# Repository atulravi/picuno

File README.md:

# PicUNO Series Of Boards By AtrivaTECH

AtrivaTECH Aims to bring the latest and greatest processors, chipsets and microcontrollers in the Custom PicUNO form factor derived from the Arduino UNO Form Factor. 

The PicUNO Line-Up of Open Source boards is as follows:
## Boards
1) RP2040 - https://github.com/atulravi/picuno/tree/main/RP2040
## Shields 
1) Lattice ICE50UP5K FPGA Shield - https://github.com/atulravi/picuno-ice
<br>
Current Version Under Test: V3.0.0 (RP2040)

## Information:

As development is consistent, documenting it, is not. To combat the same, various repositories and their purposes are given below. You may Follow the ones of choice to be notified when latest versions/updates are pushed.
1) Circuit Python port: https://github.com/atulravi/circuitpython
2) MicroPython Port: https://github.com/AtrivaTECH/micropython/tree/master
3) Arduino IDE Library: https://github.com/AtrivaTECH/AtrivaTECH_PicUNO
4) Documentation: https://github.com/AtrivaTECH/picuno-documentation
5) Project Repository: https://github.com/AtrivaTECH/picuno-projects
6) FPGA Shield: https://github.com/AtrivaTECH/picuno-ice

## Honorable Certifications:

## In The Press

Hackster.io- "Atul Ravi's PicUNO is a Pico-style RP2040 board in the popular Arduino form factor with extra features."

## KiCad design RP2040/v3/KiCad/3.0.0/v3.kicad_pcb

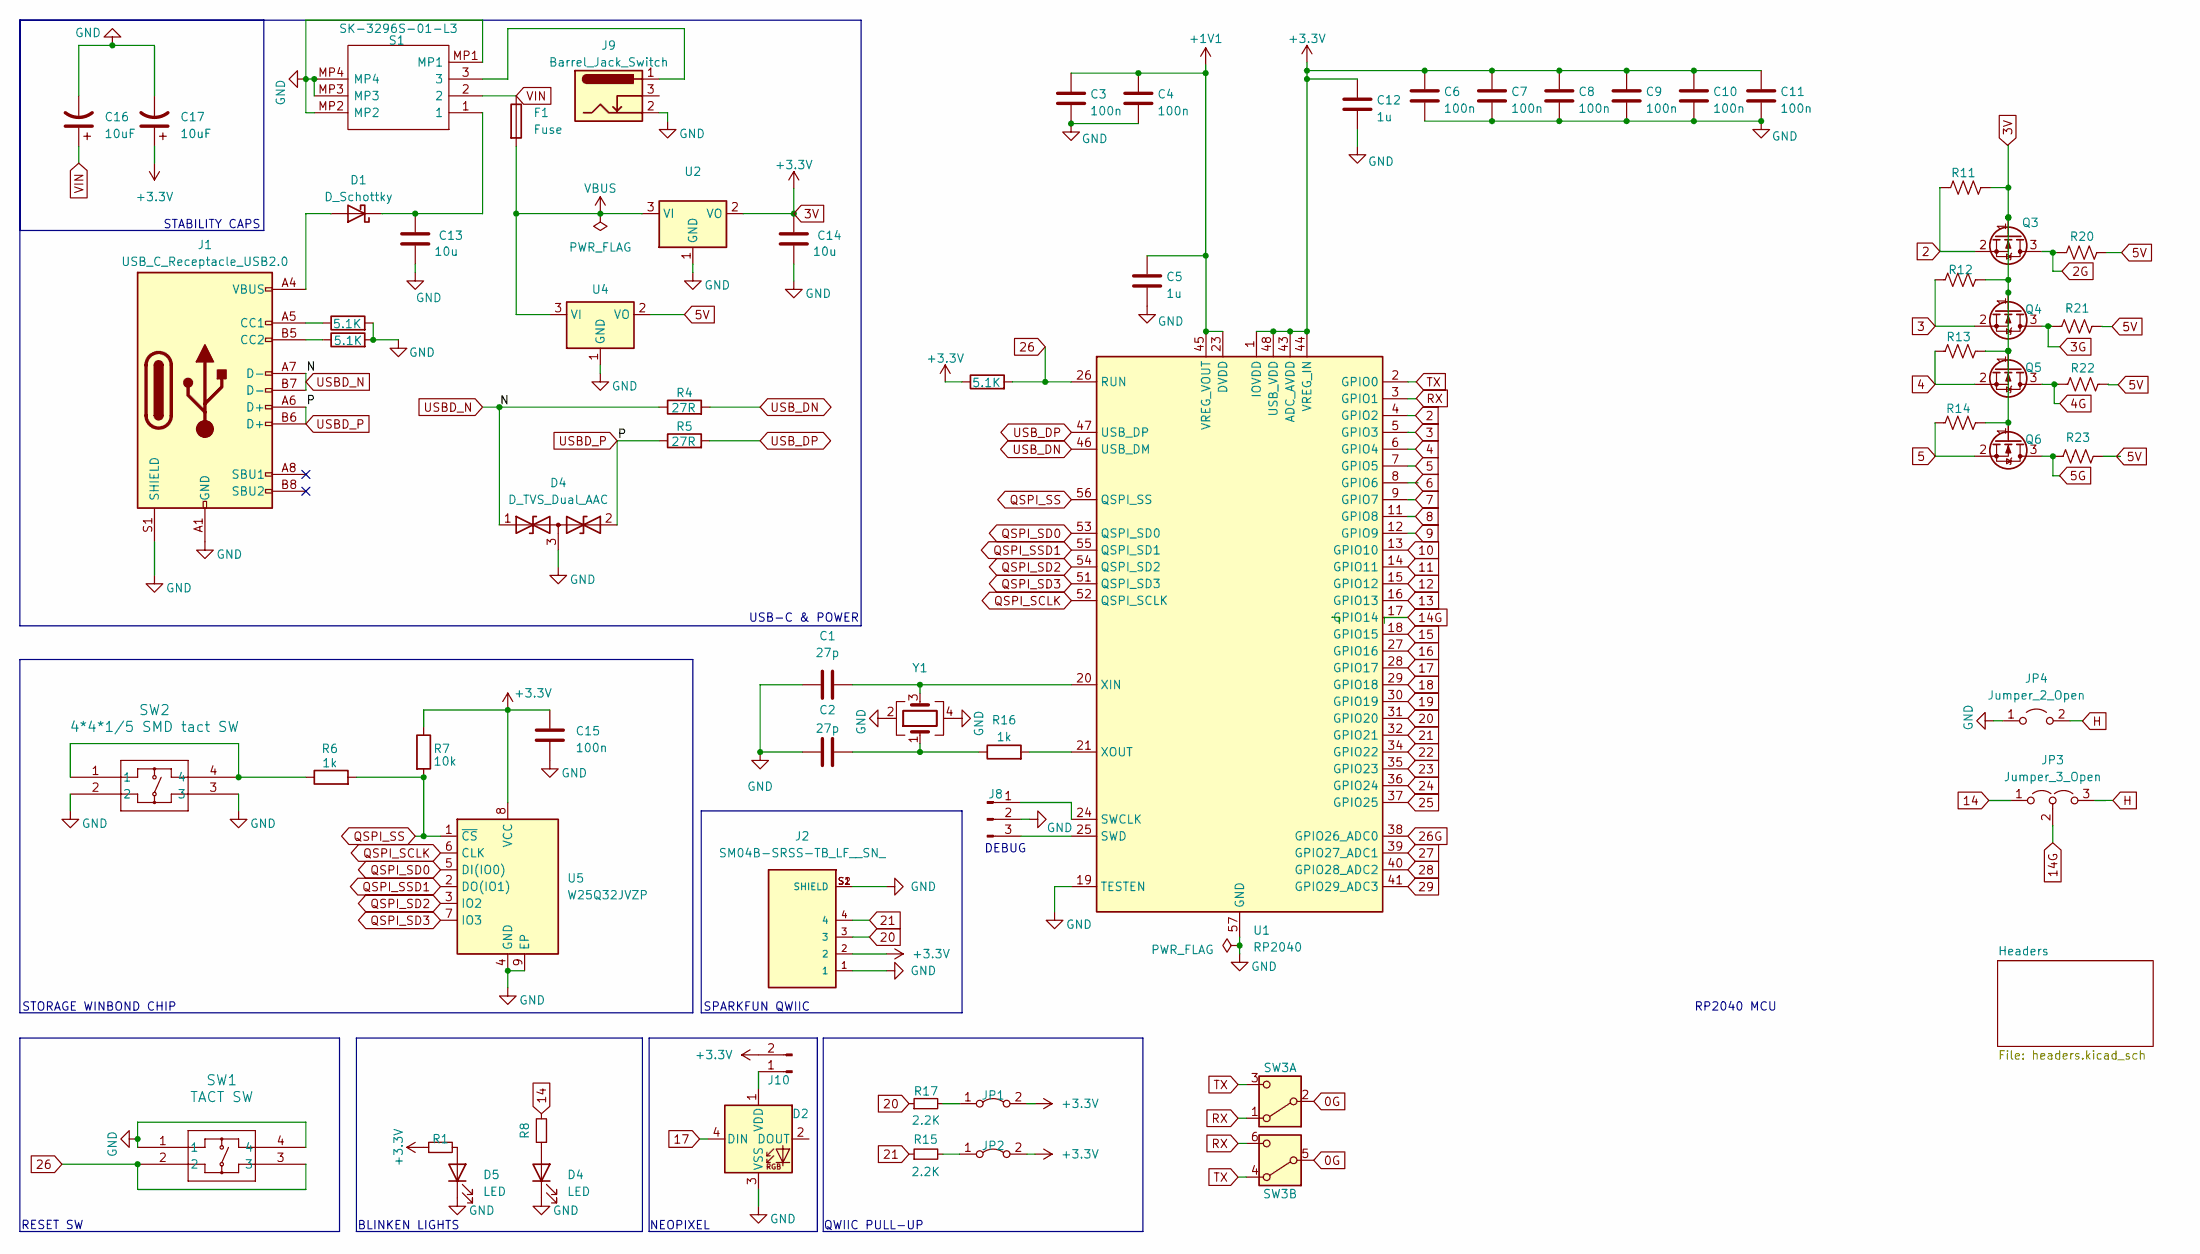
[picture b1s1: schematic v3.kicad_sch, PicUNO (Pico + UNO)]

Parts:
C1, C2: 27p; C_0402_1005Metric_Pad0.74x0.62mm_HandSolder
C3, C4, C6, C7, C8, C9, C10, C11, C15: 100n; C_0402_1005Metric_Pad0.74x0.62mm_HandSolder
C5, C12: 1u; C_0402_1005Metric_Pad0.74x0.62mm_HandSolder
C13, C14: 10u; C_0402_1005Metric_Pad0.74x0.62mm_HandSolder
C16, C17: 10uF; CP_Elec_4x5.4; LCSC C4747971
D1: D_Schottky; D_SOD-128
D2: WS2812B; LED_WS2812B_PLCC4_5.0x5.0mm_P3.2mm
D4: D_TVS_Dual_AAC; SOT-23
D5: LED; LED_0805_2012Metric_Pad1.15x1.40mm_HandSolder
F1: Fuse; Fuse_1206_3216Metric_Pad1.42x1.75mm_HandSolder
J1: USB_C_Receptacle_USB2.0; USB_C_Receptacle_G-Switch_GT-USB-7010ASV
J2: SM04B-SRSS-TB_LF__SN_; JST_SM04B-SRSS-TB_LF__SN_
J8: Conn_01x03_Pin; PinSocket_1x03_P2.54mm_Vertical
J9: Barrel_Jack_Switch; BarrelJack_Horizontal
J10: Conn_01x02_Pin; PinHeader_1x02_P2.54mm_Vertical
JP1, JP2: Jumper_2_Bridged; SolderJumper-2_P1.3mm_Open_RoundedPad1.0x1.5mm
JP3: Jumper_3_Open; SolderJumper-3_P1.3mm_Open_Pad1.0x1.5mm
JP4: Jumper_2_Open; SolderJumper-2_P1.3mm_Open_RoundedPad1.0x1.5mm
Q3, Q4, Q5, Q6: BSS138; SOT-23
R1, R8: 220; R_0402_1005Metric_Pad0.72x0.64mm_HandSolder
R2, R3, R33: 5.1K; R_0402_1005Metric_Pad0.72x0.64mm_HandSolder
R4, R5: 27R; R_0402_1005Metric_Pad0.72x0.64mm_HandSolder
R6, R16: 1k; R_0402_1005Metric_Pad0.72x0.64mm_HandSolder
R7: 10k; R_0402_1005Metric_Pad0.72x0.64mm_HandSolder
R11, R12, R13, R14, R20, R21, R22, R23: 10K; R_0402_1005Metric_Pad0.72x0.64mm_HandSolder
R15, R17: 2.2K; R_0402_1005Metric_Pad0.72x0.64mm_HandSolder
S1: SK-3296S-01-L3; SK3296S01L3; Manufacturer_Part_Number SK-3296S-01-L3
SW1: TACT SW; SW_SPST_TL3342
SW2: 4*4*1/5 SMD tact SW; SW_SPST_TL3342
SW3: SW_DPDT_x2; SW_CL-SB-22A-02T; MFG Part No C2904912
U1: RP2040; QFN-56-1EP_7x7mm_P0.4mm_EP3.2x3.2mm
U2: AZ1117CH-3.3TRG1 SOT223-3; SOT-223-3_TabPin2
U4: AMS1117-5.0; SOT-223-3_TabPin2
U5: W25Q32JVZP; WSON-8-1EP_6x5mm_P1.27mm_EP3.4x4.3mm
Y1: \YSX321SL 12 Mhz; Crystal_SMD_3225-4Pin_3.2x2.5mm

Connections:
0G: SW3.2 (B), SW3.5 (B)
2: Q3.2 (S), R11.1, U1.4 (GPIO2)
2G: Q3.3 (D), R20.1
3: Q4.2 (S), R12.1, U1.5 (GPIO3)
3G: Q4.3 (D), R21.1
3V: C6.1, C7.1, C8.1, C9.1, C10.1, C11.1, C12.1, C14.1, C15.1, C17.1, J2.2, J10.2, JP1.2 (B), JP2.2 (B), Q3.1 (G), Q4.1 (G), Q5.1 (G), Q6.1 (G), R1.1, R7.1, R11.2, R12.2, R13.2, R14.2, R33.1, U1.1 (IOVDD), U1.10 (IOVDD), U1.22 (IOVDD), U1.33 (IOVDD), U1.42 (IOVDD), U1.43 (ADC_AVDD), U1.44 (VREG_IN), U1.48 (USB_VDD), U1.49 (IOVDD), U2.2 (VO), U5.8 (VCC); also elsewhere on the board
4: Q5.2 (S), R13.1, U1.6 (GPIO4)
4G: Q5.3 (D), R22.1
5: Q6.2 (S), R14.1, U1.7 (GPIO5)
5G: Q6.3 (D), R23.1
5V: R20.2, R21.2, R22.2, R23.2, U4.2 (VO); also elsewhere on the board
6: U1.8 (GPIO6)
7: U1.9 (GPIO7)
8: U1.11 (GPIO8)
9: U1.12 (GPIO9)
10: U1.13 (GPIO10)
11: U1.14 (GPIO11)
12: U1.15 (GPIO12)
13: U1.16 (GPIO13)
14: JP3.1 (A), R8.2
14G: JP3.2 (C), U1.17 (GPIO14)
15: U1.18 (GPIO15)
16: U1.27 (GPIO16)
17: D2.4 (DIN), U1.28 (GPIO17); also elsewhere on the board
18: U1.29 (GPIO18)
19: U1.30 (GPIO19)
20: J2.3, R17.1, U1.31 (GPIO20); also elsewhere on the board
21: J2.4, R15.1, U1.32 (GPIO21); also elsewhere on the board
22: U1.34 (GPIO22)
23: U1.35 (GPIO23)
24: U1.36 (GPIO24); also elsewhere on the board
25: U1.37 (GPIO25); also elsewhere on the board
26: R33.2, SW1.2, SW1.3, U1.26 (RUN); also elsewhere on the board
26G: U1.38 (GPIO26_ADC0)
27: U1.39 (GPIO27_ADC1)
28: U1.40 (GPIO28_ADC2)
29: U1.41 (GPIO29_ADC3)
+1V1: C3.1, C4.1, C5.1, U1.23 (DVDD), U1.45 (VREG_VOUT), U1.50 (DVDD)
H: JP3.3 (B), JP4.2 (B)
unnamed: C2.2, R16.1, Y1.1
unnamed: D1.2 (A), J1.A4 (VBUS), J1.A9 (VBUS), J1.B4 (VBUS), J1.B9 (VBUS)
unnamed: C13.1, D1.1 (K), S1.1
unnamed: D2.1 (VDD), J10.1
unnamed: D5.2 (A), R1.2
unnamed: J1.A5 (CC1), R2.1
unnamed: J1.B5 (CC2), R3.1
unnamed: J8.1, U1.24 (SWCLK)
unnamed: J8.3, U1.25 (SWD)
unnamed: J9.1, S1.3
unnamed: JP1.1 (A), R17.2
unnamed: JP2.1 (A), R15.2
unnamed: R6.1, SW2.1, SW2.4
unnamed: C1.2, U1.20 (XIN), Y1.3
unnamed: R16.2, U1.21 (XOUT)
QSPI_SCLK: U1.52 (QSPI_SCLK), U5.6 (CLK)
QSPI_SD0: U1.53 (QSPI_SD0), U5.5 (DI(IO0))
QSPI_SD2: U1.54 (QSPI_SD2), U5.3 (IO2)
QSPI_SD3: U1.51 (QSPI_SD3), U5.7 (IO3)
QSPI_SS: R6.2, R7.2, U1.56 (QSPI_SS), U5.1 (~CS)
QSPI_SSD1: U1.55 (QSPI_SD1), U5.2 (DO(IO1))
RX: SW3.1 (A), SW3.6 (C), U1.3 (GPIO1)
TX: SW3.3 (C), SW3.4 (A), U1.2 (GPIO0)
USB_DN: R4.2, U1.46 (USB_DM)
USB_DP: R5.2, U1.47 (USB_DP)
VBUS: F1.2, U2.3 (VI), U4.3 (VI)
VIN: C16.1, F1.1, S1.2; also elsewhere on the board

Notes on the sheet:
NEOPIXEL
RP2040 MCU
SPARKFUN QWIIC
STABILITY CAPS
RESET SW
DEBUG
STORAGE WINBOND CHIP
QWIIC PULL-UP
BLINKEN LIGHTS
USB-C & POWER

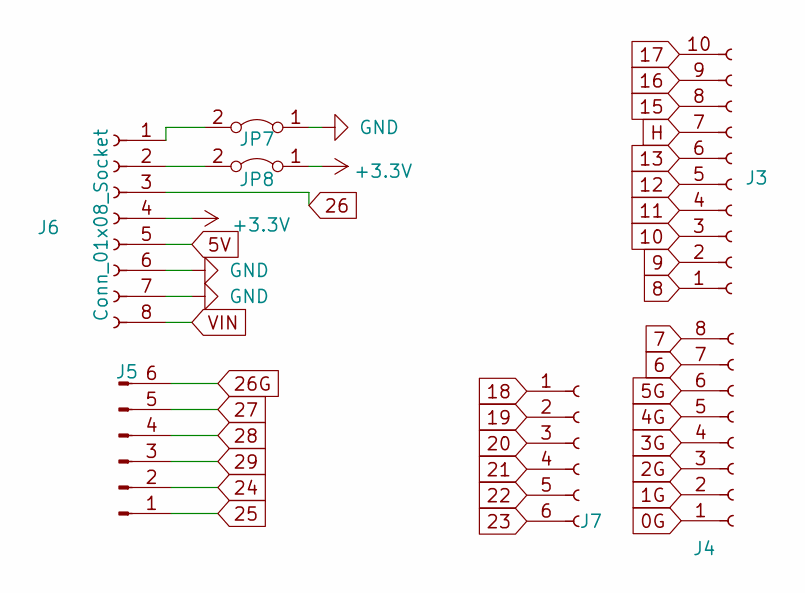
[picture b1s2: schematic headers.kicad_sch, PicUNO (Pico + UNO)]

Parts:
J3: Conn_01x10_Socket; PinSocket_1x10_P2.54mm_Vertical
J4, J6: Conn_01x08_Socket; PinSocket_1x08_P2.54mm_Vertical
J5: Conn_01x06_Pin; PinSocket_1x06_P2.54mm_Vertical
J7: Conn_01x06_Socket; PinSocket_1x06_P2.54mm_Vertical
JP7, JP8: Jumper_2_Bridged; SolderJumper-2_P1.3mm_Open_RoundedPad1.0x1.5mm

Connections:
3V: J6.4, JP8.1 (A); also elsewhere on the board
5V: J6.5; also elsewhere on the board
17: J3.10; also elsewhere on the board
20: J7.3; also elsewhere on the board
21: J7.4; also elsewhere on the board
24: J5.2; also elsewhere on the board
25: J5.1; also elsewhere on the board
26: J6.3; also elsewhere on the board
unnamed 67: J6.1, JP7.2 (B); also elsewhere on the board
unnamed 68: J6.2, JP8.2 (B); also elsewhere on the board
VIN: J6.8; also elsewhere on the board

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
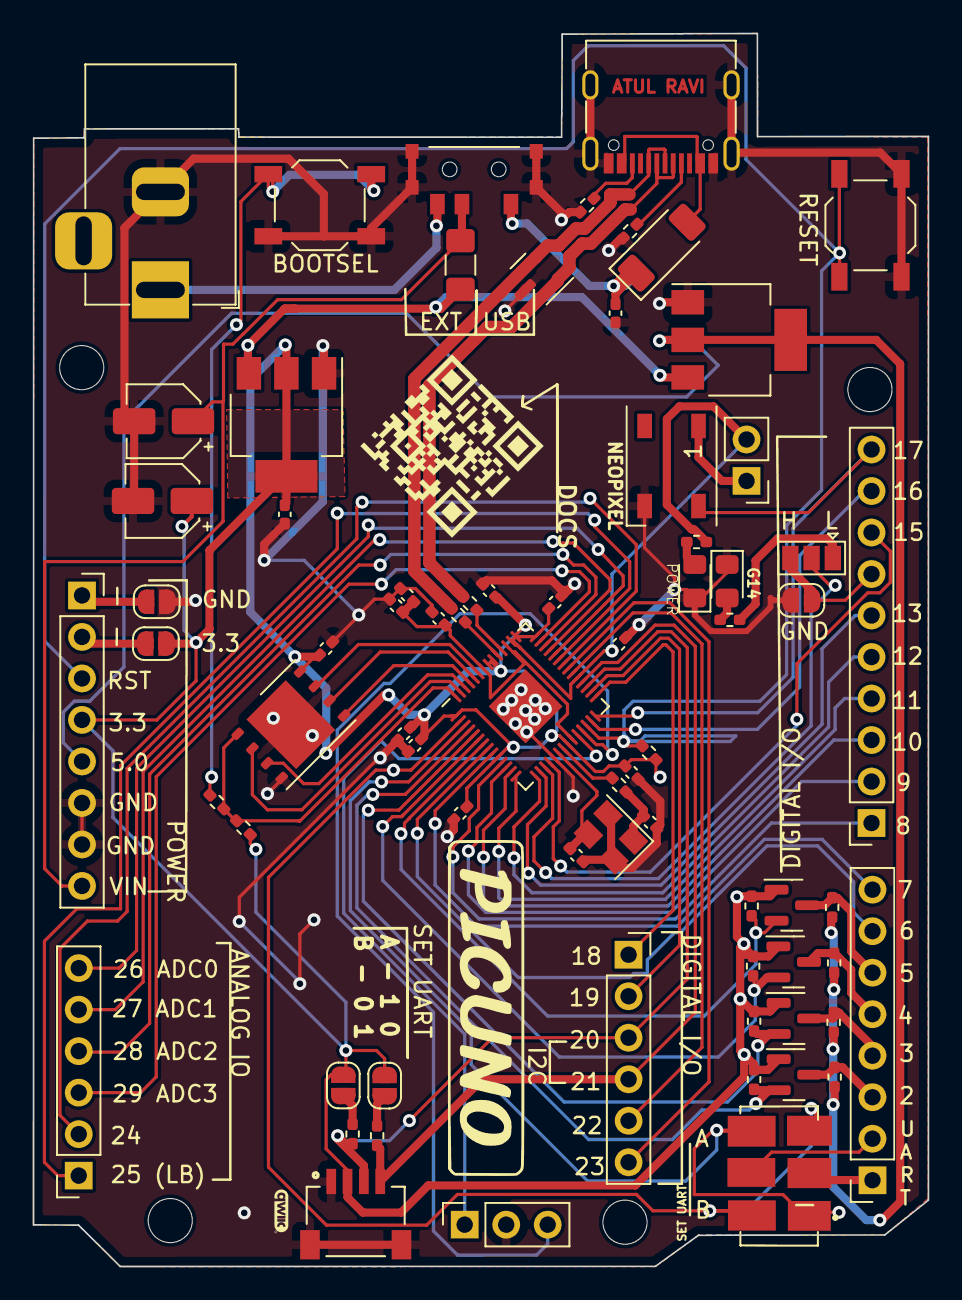
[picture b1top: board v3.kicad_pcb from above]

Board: 2 copper layers, 54.8 x 75.5 mm, 75 parts (0 on the bottom side), 54 nets.

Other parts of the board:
D3: D_TVS_Dual_AAC; SOT-23
JP5, JP6: Jumper_2_Bridged; SolderJumper-2_P1.3mm_Open_RoundedPad1.0x1.5mm
REF1**, REF2**, REF3**: MountingHole_2.7mm_M2.5_ISO14580

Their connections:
3V: JP5.1 (A); also elsewhere on the board
unnamed 67: JP6.2 (B); also elsewhere on the board
unnamed 68: JP5.2 (B); also elsewhere on the board

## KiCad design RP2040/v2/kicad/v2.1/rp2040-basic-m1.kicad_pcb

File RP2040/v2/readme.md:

Files of V2 including KiCad files added. Will be updated periodically when chanes are made. V2 also has 2 additional LEDs and minor issues in V1 fixed in V2!

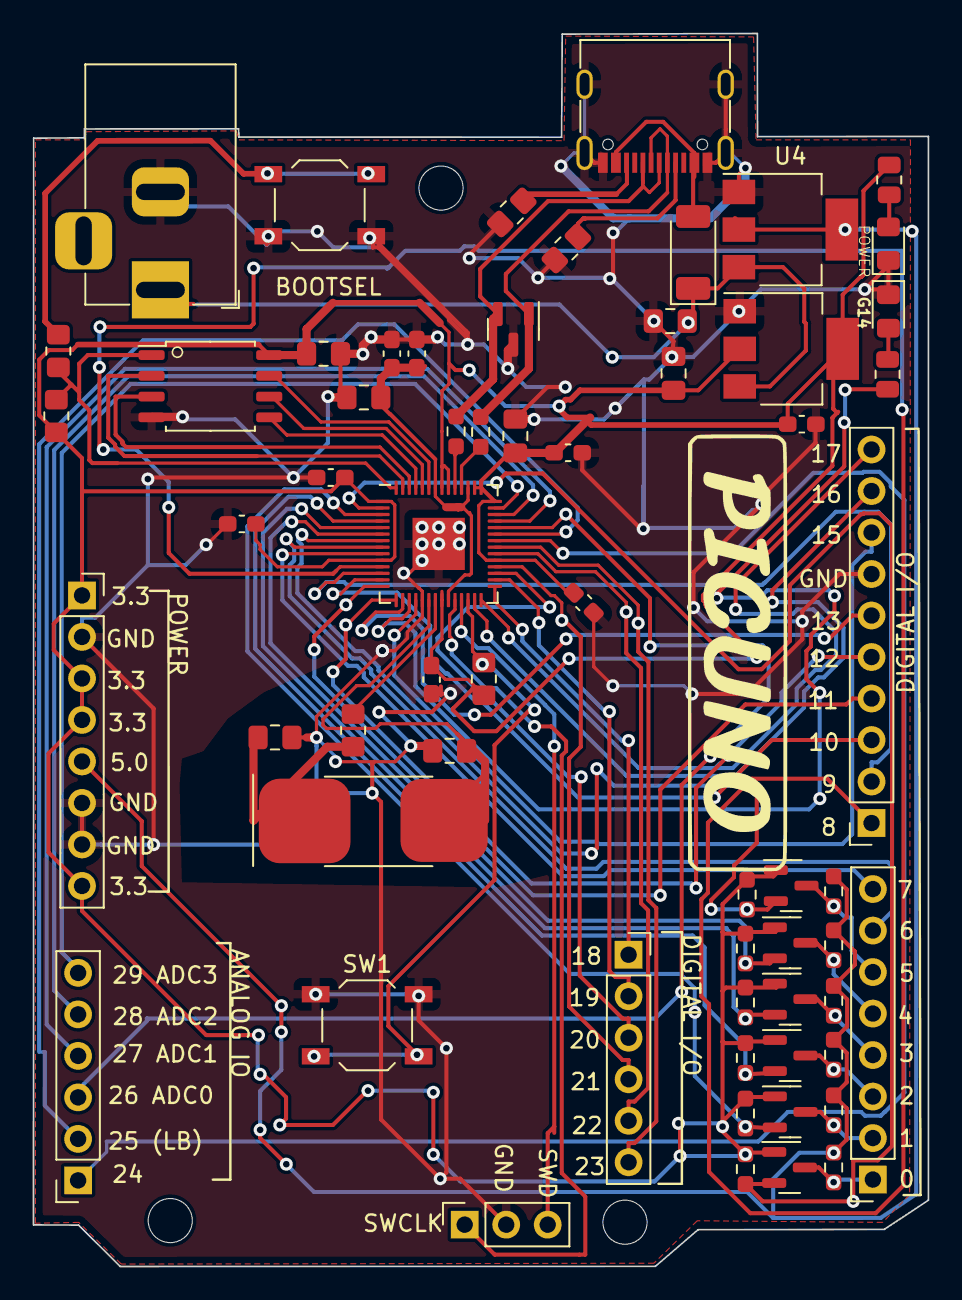
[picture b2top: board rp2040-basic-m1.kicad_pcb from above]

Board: 2 copper layers, 54.8 x 75.5 mm, 62 parts (0 on the bottom side), 63 nets.

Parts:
C1, C2: 27p; C_0805_2012Metric_Pad1.18x1.45mm_HandSolder
C3, C4, C6, C7, C8, C9, C10, C11: 100n; C_0603_1608Metric_Pad1.08x0.95mm_HandSolder
C5, C12: 1u; C_0805_2012Metric_Pad1.18x1.45mm_HandSolder
C13, C14: 10u; C_0805_2012Metric_Pad1.18x1.45mm_HandSolder
C15: 100n; C_0805_2012Metric_Pad1.18x1.45mm_HandSolder
D1: D_Schottky; D_SOD-128
D3: D_TVS_Dual_AAC; SOT-23
D4, D5: LED; LED_0805_2012Metric_Pad1.15x1.40mm_HandSolder
J1: USB_C_Receptacle_USB2.0; USB_C_Receptacle_G-Switch_GT-USB-7010ASV
J3: Conn_01x10_Socket; PinSocket_1x10_P2.54mm_Vertical
J4, J6: Conn_01x08_Socket; PinSocket_1x08_P2.54mm_Vertical
J5: Conn_01x06_Pin; PinSocket_1x06_P2.54mm_Vertical
J7: Conn_01x06_Socket; PinSocket_1x06_P2.54mm_Vertical
J8: Conn_01x03_Pin; PinSocket_1x03_P2.54mm_Vertical
J9: Barrel_Jack_Switch; BarrelJack_Horizontal
Q1, Q2, Q3, Q4, Q5, Q6: BSS138; SOT-23
R1, R8: R_Small; R_0805_2012Metric
R2, R3, R33: 5.1K; R_0805_2012Metric_Pad1.20x1.40mm_HandSolder
R4, R5: 27R; R_0603_1608Metric_Pad0.98x0.95mm_HandSolder
R6, R16: 1k; R_0805_2012Metric_Pad1.20x1.40mm_HandSolder
R7: 10k; R_0805_2012Metric_Pad1.20x1.40mm_HandSolder
R9, R10, R11, R12, R13, R14, R18, R19, R20, R21, R22, R23: 10K; R_0603_1608Metric_Pad0.98x0.95mm_HandSolder
SW1, SW2: TACT SW; SW_SPST_TL3342
U1: RP2040; QFN-56-1EP_7x7mm_P0.4mm_EP3.2x3.2mm
U2: AZ1117CH-3.3TRG1 SOT223-3; SOT-223-3_TabPin2
U3: W25Q128JVS; SOIC-8_5.23x5.23mm_P1.27mm
U4: AMS1117-5.0; SOT-223-3_TabPin2
Y1: Crystal 12 Mhz; Crystal_SMD_SeikoEpson_MA505-2Pin_12.7x5.1mm_HandSoldering

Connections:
3V: C6.1, C7.1, C8.1, C9.1, C10.1, C11.1, C12.1, C14.1, C15.1, J6.1, J6.3, J6.4, J6.8, Q1.1 (G), Q2.1 (G), Q3.1 (G), Q4.1 (G), Q5.1 (G), Q6.1 (G), R1.1, R7.1, R9.2, R10.2, R11.2, R12.2, R13.2, R14.2, R33.1, U1.1 (IOVDD), U1.10 (IOVDD), U1.22 (IOVDD), U1.33 (IOVDD), U1.42 (IOVDD), U1.43 (ADC_AVDD), U1.44 (VREG_IN), U1.48 (USB_VDD), U1.49 (IOVDD), U2.2 (VO), U3.8 (VCC)
5V: J6.5, R18.2, R19.2, R20.2, R21.2, R22.2, R23.2, U4.2 (VO)
14: R8.2, U1.17 (GPIO14)
26: R33.2, SW1.2, U1.26 (RUN)
+1V1: C3.1, C4.1, C5.1, U1.23 (DVDD), U1.45 (VREG_VOUT), U1.50 (DVDD)
/USB1_DN: D3.1 (A1), J1.A7 (D-), J1.B7 (D-), R4.1
/USB1_DP: D3.2 (A2), J1.A6 (D+), J1.B6 (D+), R5.1
GND: C1.1, C2.1, C3.2, C4.2, C5.2, C6.2, C7.2, C8.2, C9.2, C10.2, C11.2, C12.2, C13.2, C14.2, C15.2, D3.3 (common), D4.1 (K), D5.1 (K), J1.A1 (GND), J1.A12 (GND), J1.B1 (GND), J1.B12 (GND), J1.S1 (SHIELD), J3.7, J6.2, J6.6, J6.7, J8.2, J9.2, R2.2, R3.2, SW1.1, SW2.2, U1.19 (TESTEN), U1.57 (GND), U2.1 (GND), U3.4 (GND), U4.1 (GND)
unnamed: C2.2, R16.1, Y1.1
unnamed: D1.2 (A), J1.A4 (VBUS), J1.A9 (VBUS), J1.B4 (VBUS), J1.B9 (VBUS)
unnamed: D4.2 (A), R8.1
unnamed: D5.2 (A), R1.2
unnamed: J1.A5 (CC1), R2.1
unnamed: J1.B5 (CC2), R3.1
unnamed: J3.1, U1.11 (GPIO8)
unnamed: J3.2, U1.12 (GPIO9)
unnamed: J3.3, U1.13 (GPIO10)
unnamed: J3.4, U1.14 (GPIO11)
unnamed: J3.5, U1.15 (GPIO12)
unnamed: J3.6, U1.16 (GPIO13)
unnamed: J3.8, U1.18 (GPIO15)
unnamed: J3.9, U1.27 (GPIO16)
unnamed: J3.10, U1.28 (GPIO17)
unnamed: J4.1, Q1.3 (D), R18.1
unnamed: J4.2, Q2.3 (D), R19.1
unnamed: J4.3, Q3.3 (D), R20.1
unnamed: J4.4, Q4.3 (D), R21.1
unnamed: J4.5, Q5.3 (D), R22.1
unnamed: J4.6, Q6.3 (D), R23.1
unnamed: J4.7, U1.8 (GPIO6)
unnamed: J4.8, U1.9 (GPIO7)
unnamed: J5.1, U1.36 (GPIO24)
unnamed: J5.2, U1.37 (GPIO25)
unnamed: J5.3, U1.38 (GPIO26_ADC0)
unnamed: J5.4, U1.39 (GPIO27_ADC1)
unnamed: J5.5, U1.40 (GPIO28_ADC2)
unnamed: J5.6, U1.41 (GPIO29_ADC3)
unnamed: J7.1, U1.29 (GPIO18)
unnamed: J7.2, U1.30 (GPIO19)
unnamed: J7.3, U1.31 (GPIO20)
unnamed: J7.4, U1.32 (GPIO21)
unnamed: J7.5, U1.34 (GPIO22)
unnamed: J7.6, U1.35 (GPIO23)
unnamed: J8.1, U1.24 (SWCLK)
unnamed: J8.3, U1.25 (SWD)
unnamed: Q1.2 (S), R9.1, U1.2 (GPIO0)
unnamed: Q2.2 (S), R10.1, U1.3 (GPIO1)
unnamed: Q3.2 (S), R11.1, U1.4 (GPIO2)
unnamed: Q4.2 (S), R12.1, U1.5 (GPIO3)
unnamed: Q5.2 (S), R13.1, U1.6 (GPIO4)
unnamed: Q6.2 (S), R14.1, U1.7 (GPIO5)
unnamed: R6.1, SW2.1
unnamed: C1.2, U1.20 (XIN), Y1.2
unnamed: R16.2, U1.21 (XOUT)
QSPI_SCLK: U1.52 (QSPI_SCLK), U3.6 (CLK)
QSPI_SD0: U1.53 (QSPI_SD0), U3.5 (DI(IO0))
QSPI_SD2: U1.54 (QSPI_SD2), U3.3 (IO2)
QSPI_SD3: U1.51 (QSPI_SD3), U3.7 (IO3)
QSPI_SS: R6.2, R7.2, U1.56 (QSPI_SS), U3.1 (~CS)
QSPI_SSD1: U1.55 (QSPI_SD1), U3.2 (DO(IO1))
USB_DN: R4.2, U1.46 (USB_DM)
USB_DP: R5.2, U1.47 (USB_DP)
VBUS: C13.1, D1.1 (K), J9.1, U2.3 (VI), U4.3 (VI)

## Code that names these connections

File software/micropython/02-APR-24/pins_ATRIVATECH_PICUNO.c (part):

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

const machine_pin_obj_t machine_pin_obj_table[NUM_BANK0_GPIOS] = {
    [0] = PIN(0, GPIO0, 0, 8, pin_GPIO0_af),
    [1] = PIN(1, GPIO1, 0, 8, pin_GPIO1_af),
    [2] = PIN(2, GPIO2, 0, 8, pin_GPIO2_af),
    [3] = PIN(3, GPIO3, 0, 8, pin_GPIO3_af),
    [4] = PIN(4, GPIO4, 0, 8, pin_GPIO4_af),
    [5] = PIN(5, GPIO5, 0, 8, pin_GPIO5_af),
    [6] = PIN(6, GPIO6, 0, 8, pin_GPIO6_af),
    [7] = PIN(7, GPIO7, 0, 8, pin_GPIO7_af),
    [8] = PIN(8, GPIO8, 0, 8, pin_GPIO8_af),
    [9] = PIN(9, GPIO9, 0, 8, pin_GPIO9_af),
    [10] = PIN(10, GPIO10, 0, 8, pin_GPIO10_af),
    [11] = PIN(11, GPIO11, 0, 8, pin_GPIO11_af),
    [12] = PIN(12, GPIO12, 0, 8, pin_GPIO12_af),
    [13] = PIN(13, GPIO13, 0, 8, pin_GPIO13_af),
    [14] = PIN(14, GPIO14, 0, 8, pin_GPIO14_af),
    [15] = PIN(15, GPIO15, 0, 8, pin_GPIO15_af),
    [16] = PIN(16, GPIO16, 0, 8, pin_GPIO16_af),
    [17] = PIN(17, GPIO17, 0, 8, pin_GPIO17_af),
    [18] = PIN(18, GPIO18, 0, 8, pin_GPIO18_af),
    [19] = PIN(19, GPIO19, 0, 8, pin_GPIO19_af),
    [20] = PIN(20, GPIO20, 0, 9, pin_GPIO20_af),
    [21] = PIN(21, GPIO21, 0, 9, pin_GPIO21_af),
    [22] = PIN(22, GPIO22, 0, 9, pin_GPIO22_af),
    [23] = PIN(23, GPIO23, 0, 9, pin_GPIO23_af),
    [24] = PIN(24, GPIO24, 0, 9, pin_GPIO24_af),
    [25] = PIN(25, GPIO25, 0, 9, pin_GPIO25_af),
    [26] = PIN(26, GPIO26, 0, 8, pin_GPIO26_af),
    [27] = PIN(27, GPIO27, 0, 8, pin_GPIO27_af),
    [28] = PIN(28, GPIO28, 0, 8, pin_GPIO28_af),
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#endif

static const mp_rom_map_elem_t machine_pin_board_pins_locals_dict_table[] = {
    { MP_ROM_QSTR(MP_QSTR_GP0), MP_ROM_PTR(pin_GPIO0) },
    { MP_ROM_QSTR(MP_QSTR_GP1), MP_ROM_PTR(pin_GPIO1) },
    { MP_ROM_QSTR(MP_QSTR_GP2), MP_ROM_PTR(pin_GPIO2) },
    { MP_ROM_QSTR(MP_QSTR_GP3), MP_ROM_PTR(pin_GPIO3) },
    { MP_ROM_QSTR(MP_QSTR_GP4), MP_ROM_PTR(pin_GPIO4) },
    { MP_ROM_QSTR(MP_QSTR_GP5), MP_ROM_PTR(pin_GPIO5) },
    { MP_ROM_QSTR(MP_QSTR_GP6), MP_ROM_PTR(pin_GPIO6) },
    { MP_ROM_QSTR(MP_QSTR_GP7), MP_ROM_PTR(pin_GPIO7) },
    { MP_ROM_QSTR(MP_QSTR_GP8), MP_ROM_PTR(pin_GPIO8) },
    { MP_ROM_QSTR(MP_QSTR_GP9), MP_ROM_PTR(pin_GPIO9) },
    { MP_ROM_QSTR(MP_QSTR_GP10), MP_ROM_PTR(pin_GPIO10) },
    { MP_ROM_QSTR(MP_QSTR_GP11), MP_ROM_PTR(pin_GPIO11) },
    { MP_ROM_QSTR(MP_QSTR_GP12), MP_ROM_PTR(pin_GPIO12) },
    { MP_ROM_QSTR(MP_QSTR_GP13), MP_ROM_PTR(pin_GPIO13) },
    { MP_ROM_QSTR(MP_QSTR_GP14), MP_ROM_PTR(pin_GPIO14) },
    { MP_ROM_QSTR(MP_QSTR_GP15), MP_ROM_PTR(pin_GPIO15) },
    { MP_ROM_QSTR(MP_QSTR_GP16), MP_ROM_PTR(pin_GPIO16) },
    { MP_ROM_QSTR(MP_QSTR_GP17), MP_ROM_PTR(pin_GPIO17) },
    { MP_ROM_QSTR(MP_QSTR_GP18), MP_ROM_PTR(pin_GPIO18) },
    { MP_ROM_QSTR(MP_QSTR_GP19), MP_ROM_PTR(pin_GPIO19) },
    { MP_ROM_QSTR(MP_QSTR_GP20), MP_ROM_PTR(pin_GPIO20) },
    { MP_ROM_QSTR(MP_QSTR_GP21), MP_ROM_PTR(pin_GPIO21) },
    { MP_ROM_QSTR(MP_QSTR_GP22), MP_ROM_PTR(pin_GPIO22) },
    { MP_ROM_QSTR(MP_QSTR_LED), MP_ROM_PTR(pin_GPIO24) },
    { MP_ROM_QSTR(MP_QSTR_GP25), MP_ROM_PTR(pin_GPIO25) },
    { MP_ROM_QSTR(MP_QSTR_GP26), MP_ROM_PTR(pin_GPIO26) },
    { MP_ROM_QSTR(MP_QSTR_GP27), MP_ROM_PTR(pin_GPIO27) },
    { MP_ROM_QSTR(MP_QSTR_GP28), MP_ROM_PTR(pin_GPIO28) },
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MP_DEFINE_CONST_DICT(machine_pin_board_pins_locals_dict, machine_pin_board_pins_locals_dict_table);

static const mp_rom_map_elem_t machine_pin_cpu_pins_locals_dict_table[] = {
    { MP_ROM_QSTR(MP_QSTR_GPIO0), MP_ROM_PTR(pin_GPIO0) },
    { MP_ROM_QSTR(MP_QSTR_GPIO1), MP_ROM_PTR(pin_GPIO1) },
    { MP_ROM_QSTR(MP_QSTR_GPIO2), MP_ROM_PTR(pin_GPIO2) },
    { MP_ROM_QSTR(MP_QSTR_GPIO3), MP_ROM_PTR(pin_GPIO3) },
    { MP_ROM_QSTR(MP_QSTR_GPIO4), MP_ROM_PTR(pin_GPIO4) },
    { MP_ROM_QSTR(MP_QSTR_GPIO5), MP_ROM_PTR(pin_GPIO5) },
    { MP_ROM_QSTR(MP_QSTR_GPIO6), MP_ROM_PTR(pin_GPIO6) },
    { MP_ROM_QSTR(MP_QSTR_GPIO7), MP_ROM_PTR(pin_GPIO7) },
    { MP_ROM_QSTR(MP_QSTR_GPIO8), MP_ROM_PTR(pin_GPIO8) },
    { MP_ROM_QSTR(MP_QSTR_GPIO9), MP_ROM_PTR(pin_GPIO9) },
    { MP_ROM_QSTR(MP_QSTR_GPIO10), MP_ROM_PTR(pin_GPIO10) },
    { MP_ROM_QSTR(MP_QSTR_GPIO11), MP_ROM_PTR(pin_GPIO11) },
    { MP_ROM_QSTR(MP_QSTR_GPIO12), MP_ROM_PTR(pin_GPIO12) },
    { MP_ROM_QSTR(MP_QSTR_GPIO13), MP_ROM_PTR(pin_GPIO13) },
    { MP_ROM_QSTR(MP_QSTR_GPIO14), MP_ROM_PTR(pin_GPIO14) },
    { MP_ROM_QSTR(MP_QSTR_GPIO15), MP_ROM_PTR(pin_GPIO15) },
    { MP_ROM_QSTR(MP_QSTR_GPIO16), MP_ROM_PTR(pin_GPIO16) },
    { MP_ROM_QSTR(MP_QSTR_GPIO17), MP_ROM_PTR(pin_GPIO17) },
    { MP_ROM_QSTR(MP_QSTR_GPIO18), MP_ROM_PTR(pin_GPIO18) },
    { MP_ROM_QSTR(MP_QSTR_GPIO19), MP_ROM_PTR(pin_GPIO19) },
    { MP_ROM_QSTR(MP_QSTR_GPIO20), MP_ROM_PTR(pin_GPIO20) },
    { MP_ROM_QSTR(MP_QSTR_GPIO21), MP_ROM_PTR(pin_GPIO21) },
    { MP_ROM_QSTR(MP_QSTR_GPIO22), MP_ROM_PTR(pin_GPIO22) },
    { MP_ROM_QSTR(MP_QSTR_GPIO23), MP_ROM_PTR(pin_GPIO23) },
    { MP_ROM_QSTR(MP_QSTR_GPIO24), MP_ROM_PTR(pin_GPIO24) },
    { MP_ROM_QSTR(MP_QSTR_GPIO25), MP_ROM_PTR(pin_GPIO25) },
    { MP_ROM_QSTR(MP_QSTR_GPIO26), MP_ROM_PTR(pin_GPIO26) },
    { MP_ROM_QSTR(MP_QSTR_GPIO27), MP_ROM_PTR(pin_GPIO27) },
    { MP_ROM_QSTR(MP_QSTR_GPIO28), MP_ROM_PTR(pin_GPIO28) },
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
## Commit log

2024-01-22 Add files via upload
    Gerbers are of V1. Kicad files are of V2
2024-01-22 Update README.md
    Added link to article on esccrasci.in
2024-01-23 Added update text
    Text added
2024-01-23 Create readme.md
    File re-arrangement
2024-01-23 Gerbers and RAR Files for fabrication UPLOADED
    All files incl gerbers and rar and zip added.
2024-01-23 Schematic uploaded to directory via UPLOAD
    Schematic uploaded to directory
2024-01-23 Create readme.md
    Info of V1 added.
2024-01-23 Photos added via UPLOAD
    Photos of V1 uploaded
2024-01-23 Assembly files BOM etc added via UPLOAD
    Files uploaded
2024-01-23 Kicad files added via UPLOAD
2024-01-25 KiCad files added via UPLOAD for V2.1
    KiCad files added via UPLOAD for V2.1
2024-01-28 V2.2 Final files added.
    Diffrential Routing errors fixed.
2024-01-28 GEBER files of V2.2 Added
    Possibly final iteration
2024-01-28 Schematic PDF added via upload
2024-01-28 readme for schematics made
2024-01-29 V2.2.1 folder created for updated PCB
2024-01-29 Kicad FIles with changes mentioned in Readme of V2.2.1 Added
2024-01-29 V2.2.1 Gerbers with changed in readme VIA UPLOAD
    V2.2.1 files with 2 less logic level shifters and India Flag under Winbond Flash added.
2024-01-29 Update README.md with strikethroughs.
    Some outdated text regarding updates struckthough
2024-02-03 Update README.md with licenses
2024-02-03 Update README.md with Licenses heading
2024-02-03 OSHW facts image added via upload
2024-02-03 OSHW png added via upload
2024-02-03 Update README.md with OSHW facts
2024-02-09 Create readme.md for 3.3V version
2024-02-09 Gerbers RAR added via upload
2024-02-09 Create readme.md for 3.3V picuno
2024-02-09 Gerber files and build files added via upload
2024-02-09 Update README.md with team
2024-02-09 Update README.md with note on file manangement
2024-02-11 Update README.md with oshwa code
2024-02-14 PCB3D file added for blender
2024-02-15 Update README.md with kicad and product pic
2024-02-16 Create readme.md with manufacuture-costs etc
2024-02-16 BOM and Fab costing calculation Excel files added.
2024-02-16 Update readme.md with campaign goal
2024-02-16 Update README.md with campaign goal text
2024-02-17 Update README.md with current proto ver
2024-02-20 Create readme.md for 2.2.3 kicad
2024-02-20 kicad files for 2.2.3 added via upload
2024-02-20 Update README.md with latest protol
2024-02-20 Update and rename fp-info-cache to old/fp-info-cache
2024-02-20 Rename fp-lib-table to old/fp-lib-table
2024-02-20 Rename freerouting.bin to old/freerouting.bin
2024-02-20 Rename sym-lib-table to old/sym-lib-table
2024-02-20 Rename rp2040-basic-m1.pdf to old/rp2040-basic-m1.pdf
2024-02-20 Rename rp2040-basic-m1.kicad_pro to old/rp2040-basic-m1.kicad_pro
2024-02-20 Rename rp2040-basic-m1.kicad_prl to old/rp2040-basic-m1.kicad_prl
2024-02-20 Rename rp2040-basic-m1 - Copy.kicad_pro to old/rp2040-basic-m1 - Copy.kicad_pro
2024-02-20 Rename rp2040-basic-m1 - Copy.kicad_prl to old/rp2040-basic-m1 - Copy.kicad_prl
2024-02-20 Rename picouno.bmp to picuno.bmp
2024-03-21 Files added
2024-03-24 Picuno 5V gerbers and Visual Place file uploaded.
2024-03-24 Gerber files of 5V 2.2.3 Edition for visualplace.
2024-03-28 POS files added
2024-03-29 Readme updated with production path
2024-04-01 software-cpython files added
2024-04-01 Circuit Python FIles added for testing
2024-04-02 MicroPython firmware files added via upload
2024-04-20 Gerbers for V2.5 Added via upload
2024-04-20 Kicad files for 2.5 added via upload
2024-04-30 Moved all files to RP2040 folder
2024-04-30 Rename README.md to README.md
2024-11-15 Update README.md
    removed Hindu Pic
